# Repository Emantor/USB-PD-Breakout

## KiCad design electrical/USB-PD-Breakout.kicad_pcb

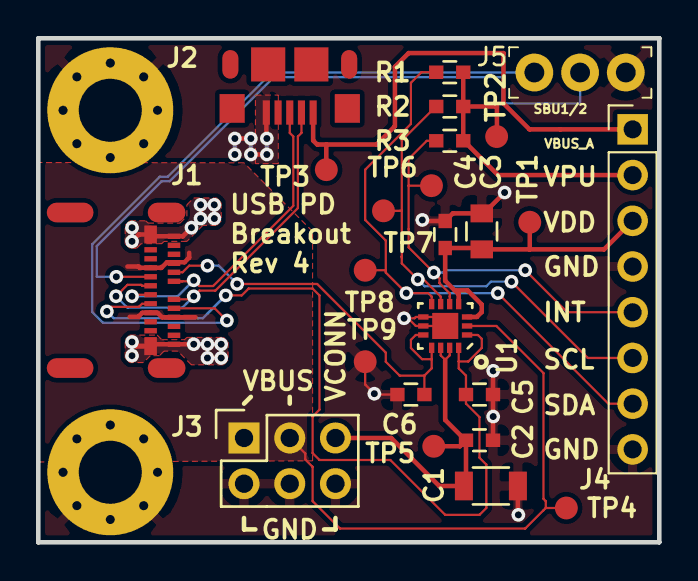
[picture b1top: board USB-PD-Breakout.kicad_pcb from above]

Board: 2 copper layers, 34.5 x 28.0 mm, 26 parts (0 on the bottom side), 15 nets.

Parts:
C1: 10uF; C_1206
C2, C4: 0.1uF; C_0603
C3: 1uF; C_0805
C5, C6: 470pF; C_0603
J1: USB-C_Female; USB-C_Female_105450-0101
J2: USB_OTG; USB_Micro-B_10118193
J3: CONN_02X03; Socket_Strip_Straight_2x03
J4: Conn_01x08_Male; Socket_Strip_Straight_1x08_Pitch2.54mm
J5: 640456-3; PinHeader_1x3_P2.54_Drill1.1mm
R1, R2, R3: 4.7k; C_0603
TP1, TP2, TP3, TP4, TP5, TP6, TP7, TP8, TP9: TEST_1P; TP
U1: FUSB302BMPX; MLP_14
X1, X2: MTHOLE; MountingHole_3.5mm_Pad_Via

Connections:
/SCL: J4.6, R2.2, TP7.1, U1.6
/SDA: J4.7, R1.2, TP8.1, U1.7
/USB20_D+: J1.A6, J1.B6, J2.3
/USB20_D-: J1.A7, J1.B7, J2.2
/USBC_CC1: C6.1, J1.A5, U1.10, U1.11
/USBC_CC2: C5.1, J1.B5, U1.1, U1.14
/~INT: J4.5, R3.2, TP6.1, U1.5
GND: C1.2, C2.2, C3.2, C4.2, C5.2, C6.2, J1.A1, J1.A12, J1.B1, J1.B12, J2.5, J3.2, J3.4, J3.6, J4.4, J4.8, J5.3, TP9.1, U1.8, U1.9, U1.15, X1.1, X2.1
unnamed: J1.A8, J5.1
unnamed: J1.B8, J5.2
VBUS_A: J2.1, J4.1, TP3.1
VBUS_C: J1.A4, J1.A9, J1.B4, J1.B9, J3.1, J3.3, TP4.1, U1.2
VCONN: C1.1, C2.1, J3.5, TP5.1, U1.12, U1.13
VDD: C3.1, C4.1, J4.3, TP1.1, U1.3, U1.4
V_PULLUP: J4.2, R1.1, R2.1, R3.1, TP2.1

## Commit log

2021-05-28 Add SBU header for Apple M1 debug UART
